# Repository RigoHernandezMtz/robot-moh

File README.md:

# Robot Moh

## Robot móvil para navegación

Este repositorio contiene los archivos necesarios para poner a funcionar el robot, como:

- Diagrama y PCB en documentos de Eagle
- Archivos de CAD del chasis en formato de Siemens Unigraphics NX 10.5
- Lista de materiales en documento de Excel, y de corte laser del chasis en PDF.
- Codigos, del arduino y de la Raspberry Pi o BeagleBone Black

### Diseño en CAD del robot

---

Diseñado por: **Ing. Gerardo Ramos Vasquez**

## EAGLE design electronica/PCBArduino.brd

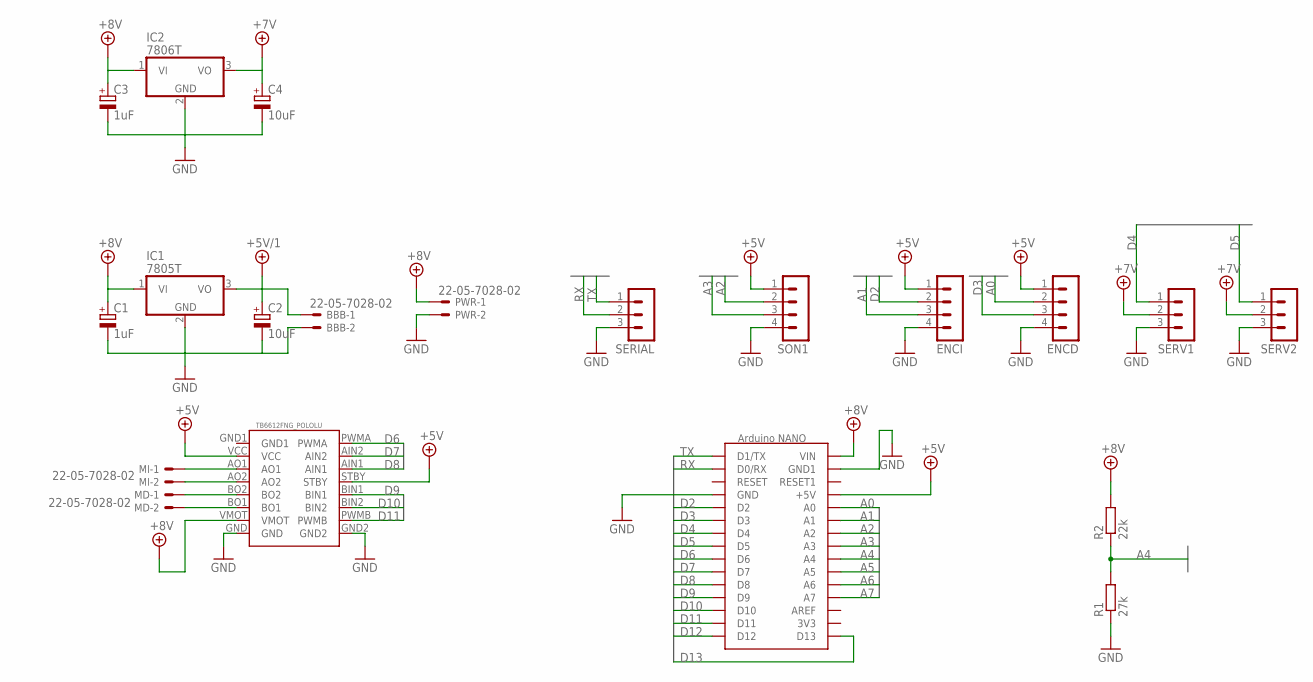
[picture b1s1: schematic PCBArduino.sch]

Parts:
BBB: 22-05-7028-02; 7395-02
C1, C3: 1uF; E2,5-7
C2, C4: 10uF; E2,5-7
ENCD: MA04-1
ENCI: MA04-1
IC1: 7805T; TO220H
IC2: 7806T; TO220H
MD: 22-05-7028-02; 7395-02
MI: 22-05-7028-02; 7395-02
PWR: 22-05-7028-02; 7395-02
R1: 27k; 0204/5
R2: 22k; 0204/5
SERIAL: MA03-1
SERV1, SERV2: MA03-1
SON1: MA04-1
U$1: ARDUINONANO; PDIP-32
U$2: TB6612FNG_POLOLU

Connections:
+5V: ENCD.1, ENCI.1, SON1.1, U$1.+5V, U$2.STBY, U$2.VCC
+5V/1: BBB.1, C2.+, IC1.3 (VO)
+7V: C4.+, IC2.3 (VO), SERV1.2, SERV2.2
+8V: C1.+, C3.+, IC1.1 (VI), IC2.1 (VI), PWR.1, R2.2, U$1.VIN, U$2.VMOT
A0: ENCD.2, U$1.A0
A1: ENCI.3, U$1.A1
A2: SON1.2, U$1.A2
A3: SON1.3, U$1.A3
A4: R1.2, R2.1, U$1.A4
A5: U$1.A5
A6: U$1.A6
A7: U$1.A7
D2: ENCI.2, U$1.D2
D3: ENCD.3, U$1.D3
D4: SERV1.1, U$1.D4
D5: SERV2.1, U$1.D5
D6: U$1.D6, U$2.PWMA
D7: U$1.D7, U$2.AIN2
D8: U$1.D8, U$2.AIN1
D9: U$1.D9, U$2.BIN1
D10: U$1.D10, U$2.BIN2
D11: U$1.D11, U$2.PWMB
D12: U$1.D12
D13: U$1.D13
GND: BBB.2, C1.-, C2.-, C3.-, C4.-, ENCD.4, ENCI.4, IC1.2 (GND), IC2.2 (GND), PWR.2, R1.1, SERIAL.3, SERV1.3, SERV2.3, SON1.4, U$1.GND, U$1.GND1, U$2.GND, U$2.GND2
unnamed: MI.1, U$2.AO1
unnamed: MI.2, U$2.AO2
unnamed: MD.1, U$2.BO2
unnamed: MD.2, U$2.BO1
RX: SERIAL.2, U$1.D0/RX
TX: SERIAL.1, U$1.D1/TX

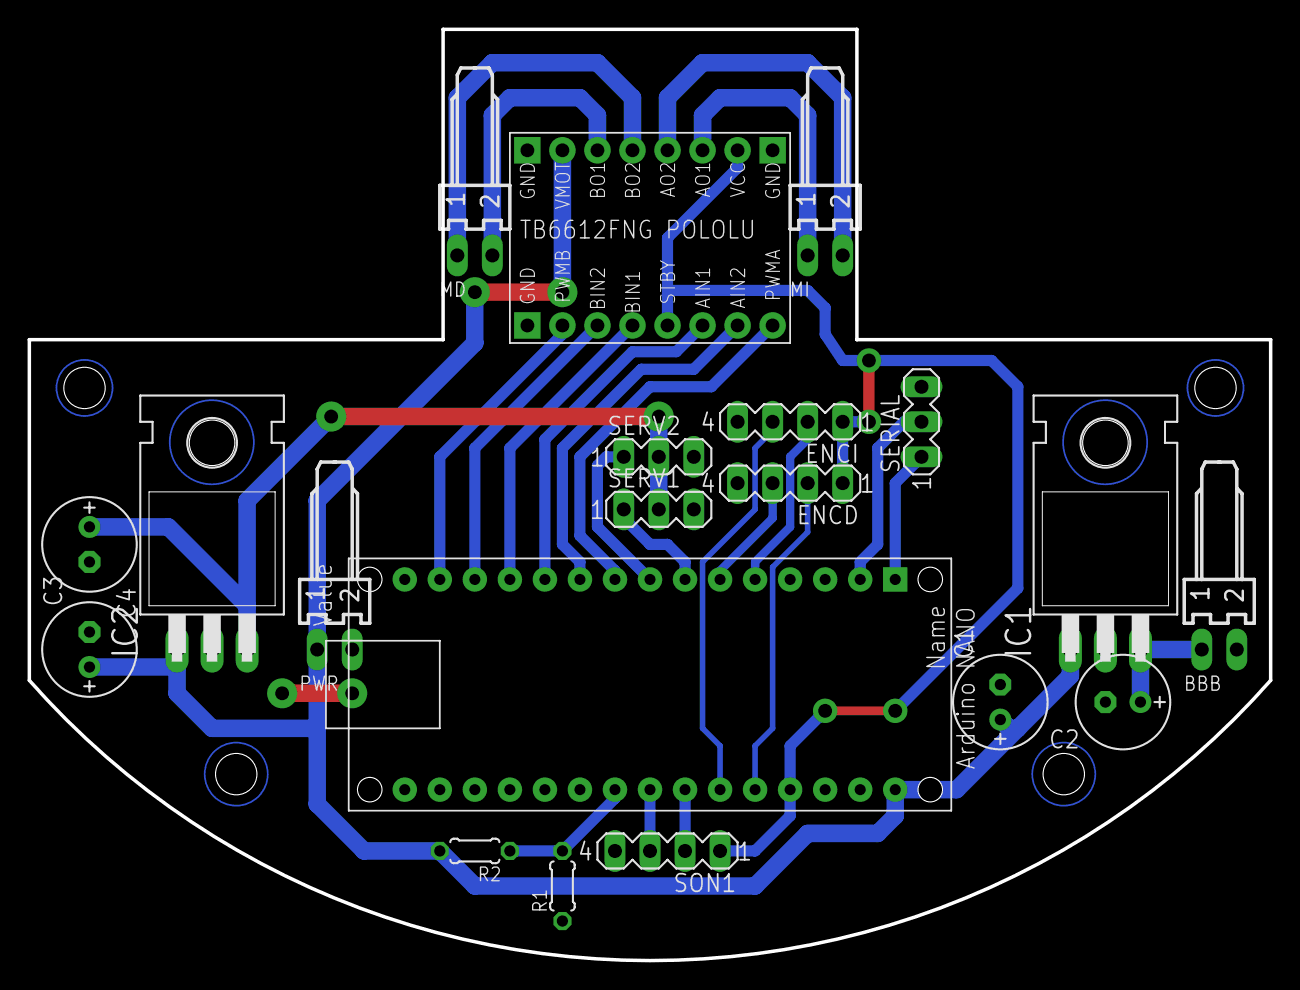
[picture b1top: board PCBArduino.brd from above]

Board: 2 copper layers, 90.0 x 67.5 mm, 20 parts (0 on the bottom side), 26 nets.

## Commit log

2019-12-02 agregando documentos del Robot Moh a gitHub
